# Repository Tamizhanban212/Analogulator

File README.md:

# Analogulator

In an era dominated by digital computation, analog computing remains relevant for specific applications that require real-time processing, low power consumption, and continuous data handling. Unlike digital calculators that rely on discrete logic and binary arithmetic, analog calculators use continuous voltage or current levels to represent data, enabling faster and more efficient computations for certain tasks.

This project, "Analog Calculator," aims to design a calculator using only analog components (e.g., op-amps, MOSFETs, resistors, capacitors) to perform mathematical operations such as addition, subtraction, multiplication, division, and advanced functions like integration and differentiation. By leveraging analog circuits, this project explores a simpler, more efficient approach to computations in specific real-world scenarios.

Hence, we have designed PCB for the analog calculator inside a 11 cm x 11 cm frame and you can see the final product shown below.

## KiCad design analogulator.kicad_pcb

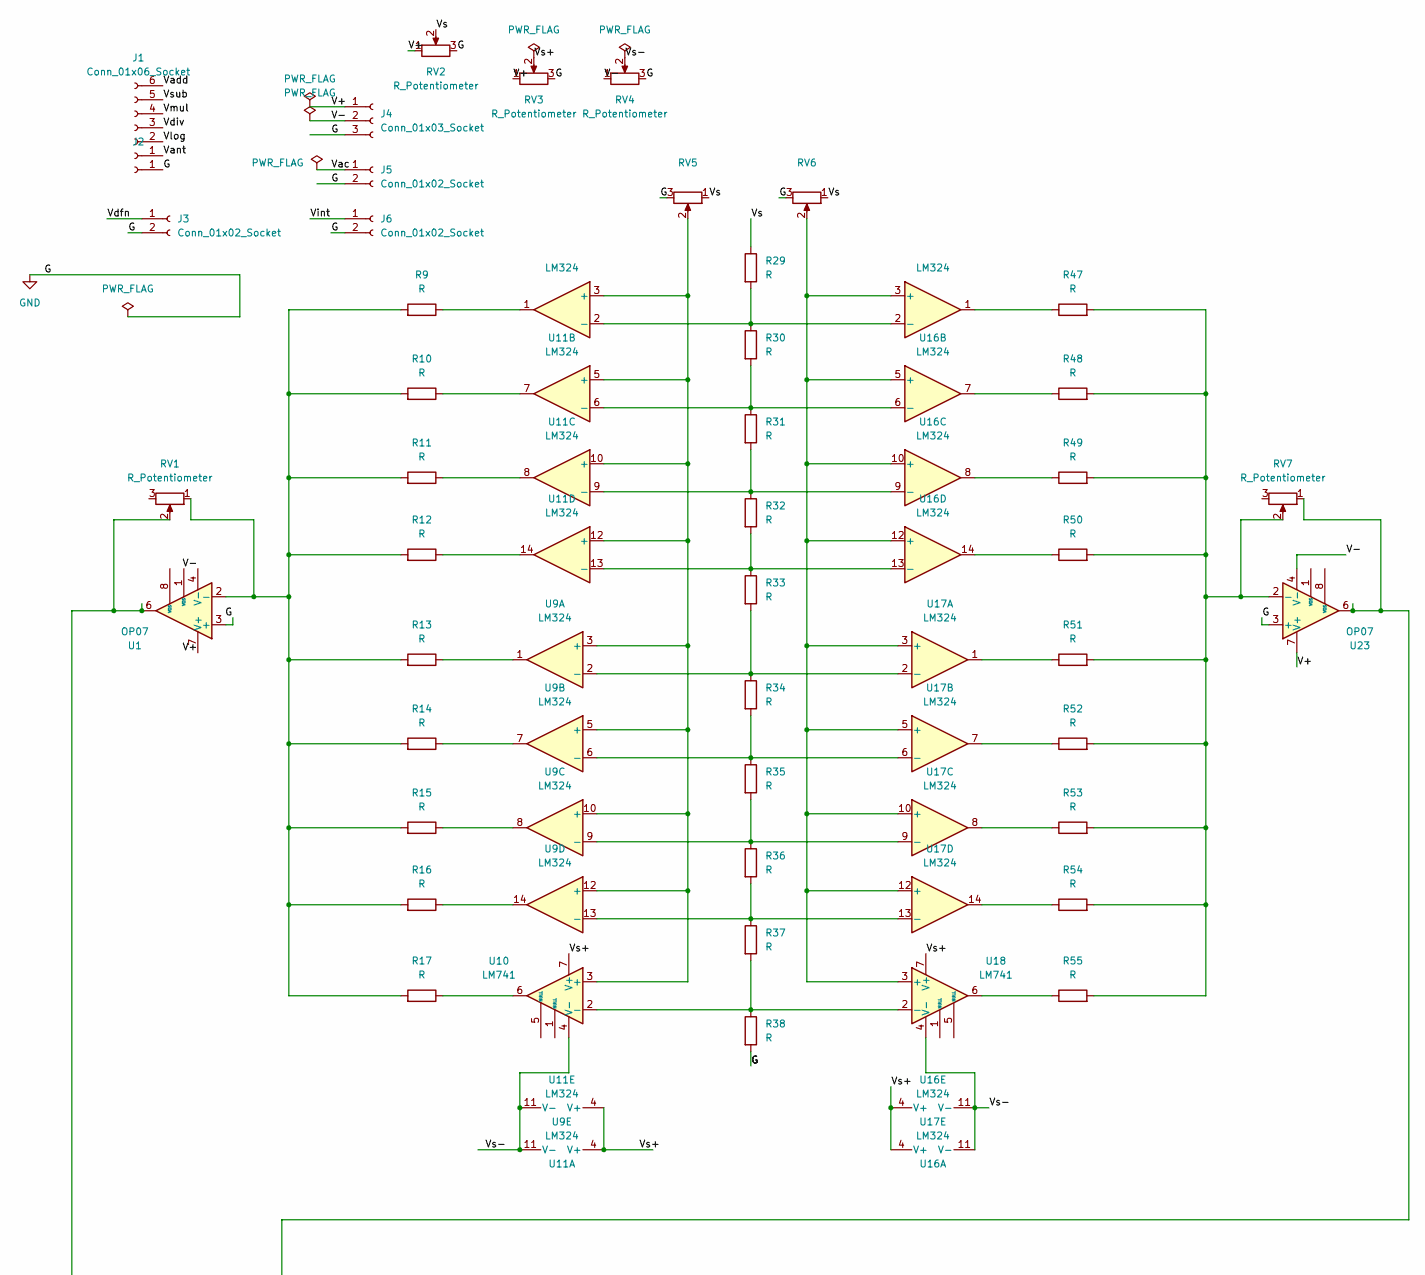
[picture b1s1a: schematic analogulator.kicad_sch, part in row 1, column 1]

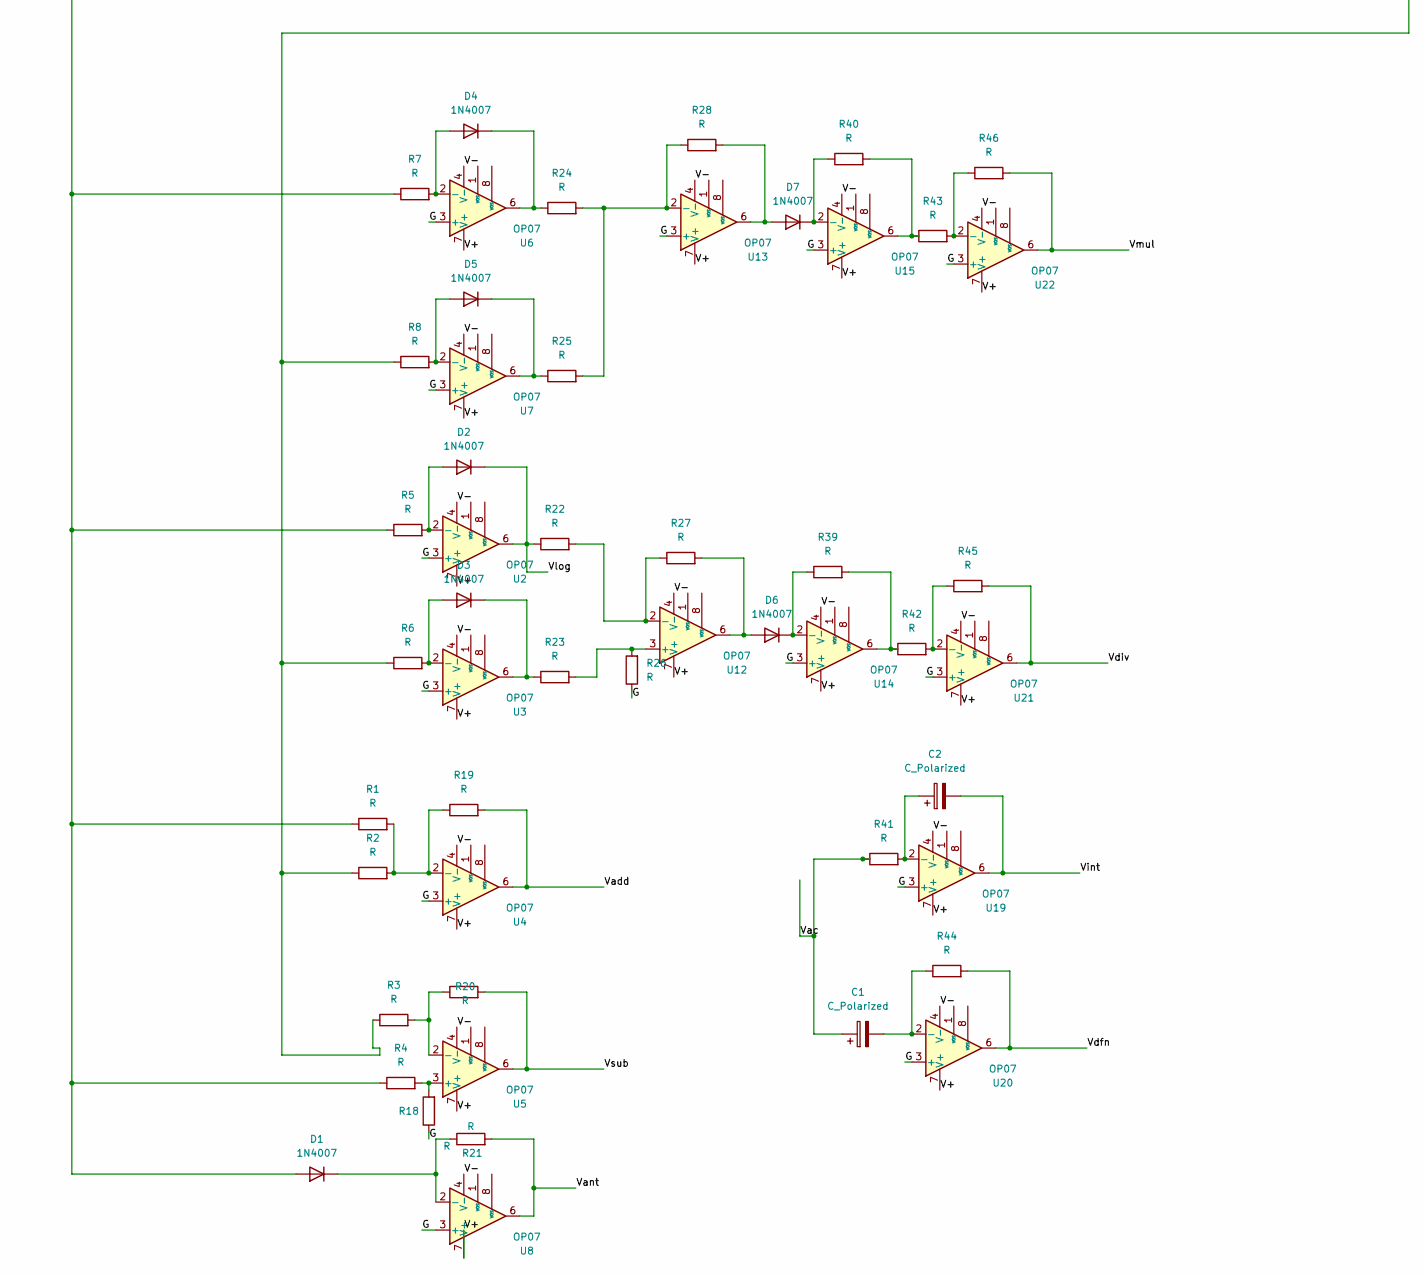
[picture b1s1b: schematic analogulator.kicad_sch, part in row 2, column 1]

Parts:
C1, C2: C_Polarized; CP_Radial_D12.5mm_P7.50mm
D1, D2, D3, D4, D5, D6, D7: 1N4007; D_DO-41_SOD81_P10.16mm_Horizontal
J1: Conn_01x06_Socket; PinSocket_1x06_P2.54mm_Vertical
J2: Conn_01x01_Socket; PinSocket_1x01_P2.54mm_Vertical
J3, J5, J6: Conn_01x02_Socket; PinSocket_1x02_P2.54mm_Vertical
J4: Conn_01x03_Socket; PinSocket_1x03_P2.54mm_Horizontal
R1, R2, R3, R4, R5, R6, R7, R8, R9, R10, R11, R12, R13, R14, R15, R16, R17, R18, R19, R20, R21, R22, R23, R24, R25, R26, R27, R28, R29, R30, R31, R32, R33, R34, R35, R36, R37, R38, R39, R40, R41, R42, R43, R44, R45, R46, R47, R48, R49, R50, R51, R52, R53, R54, R55: R; R_Axial_DIN0309_L9.0mm_D3.2mm_P12.70mm_Horizontal
RV1, RV2, RV3, RV4, RV5, RV6, RV7: R_Potentiometer; Potentiometer_Bourns_3386P_Vertical
U1, U2, U3, U4, U5, U6, U7, U8, U12, U13, U14, U15, U19, U20, U21, U22, U23: OP07; DIP-8_W7.62mm_Socket
U9, U11, U16, U17: LM324; DIP-14_W7.62mm_Socket
U10, U18: LM741; DIP-8_W7.62mm_Socket

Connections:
/V+: J4.1, RV2.1, RV3.1, U1.7 (V+), U2.7 (V+), U3.7 (V+), U4.7 (V+), U5.7 (V+), U6.7 (V+), U7.7 (V+), U8.7 (V+), U12.7 (V+), U13.7 (V+), U14.7 (V+), U15.7 (V+), U19.7 (V+), U20.7 (V+), U21.7 (V+), U22.7 (V+), U23.7 (V+)
/V-: J4.2, RV4.1, U1.4 (V-), U2.4 (V-), U3.4 (V-), U4.4 (V-), U5.4 (V-), U6.4 (V-), U7.4 (V-), U8.4 (V-), U12.4 (V-), U13.4 (V-), U14.4 (V-), U15.4 (V-), U19.4 (V-), U20.4 (V-), U21.4 (V-), U22.4 (V-), U23.4 (V-)
/Vac: C1.1, J5.1, R41.1
/Vadd: J1.6, R19.2, U4.6
/Vant: J1.1, R21.2, U8.6
/Vdfn: J3.1, R44.2, U20.6
/Vdiv: J1.3, R45.2, U21.6
/Vint: C2.2, J6.1, U19.6
/Vlog: D2.1 (K), J1.2, R22.1, U2.6
/Vmul: J1.4, R46.2, U22.6
/Vs: R29.1, RV2.2, RV5.1, RV6.1
/Vs+: RV3.2, U9.4 (V+), U10.7 (V+), U11.4 (V+), U16.4 (V+), U17.4 (V+), U18.7 (V+)
/Vs-: RV4.2, U9.11 (V-), U10.4 (V-), U11.11 (V-), U16.11 (V-), U17.11 (V-), U18.4 (V-)
/Vsub: J1.5, R20.2, U5.6
GND: J2.1, J3.2, J4.3, J5.2, J6.2, R18.1, R26.1, R38.2, RV2.3, RV3.3, RV4.3, RV5.3, RV6.3, U1.3 (+), U2.3 (+), U3.3 (+), U4.3 (+), U6.3 (+), U7.3 (+), U8.3 (+), U13.3 (+), U14.3 (+), U15.3 (+), U19.3 (+), U20.3 (+), U21.3 (+), U22.3 (+), U23.3 (+)
unnamed: D1.2 (A), R1.1, R4.1, R5.1, R7.1, RV1.2, U1.6
unnamed: D1.1 (K), R21.1, U8.2 (-)
unnamed: D2.2 (A), R5.2, U2.2 (-)
unnamed: D3.2 (A), R6.2, U3.2 (-)
unnamed: D3.1 (K), R23.1, U3.6
unnamed: D4.2 (A), R7.2, U6.2 (-)
unnamed: D4.1 (K), R24.1, U6.6
unnamed: D5.2 (A), R8.2, U7.2 (-)
unnamed: D5.1 (K), R25.1, U7.6
unnamed: D6.2 (A), R27.2, U12.6
unnamed: D6.1 (K), R39.1, U14.2 (-)
unnamed: D7.2 (A), R28.2, U13.6
unnamed: D7.1 (K), R40.1, U15.2 (-)
unnamed: R2.1, R3.1, R6.1, R8.1, RV7.1, U23.6
unnamed: R9.1, U11.1
unnamed: R10.1, U11.7
unnamed: R11.1, U11.8
unnamed: R12.1, U11.14
unnamed: R13.1, U9.1
unnamed: R14.1, U9.7
unnamed: R15.1, U9.8
unnamed: R16.1, U9.14
unnamed: R17.1, U10.6
unnamed: R39.2, R42.1, U14.6
unnamed: R40.2, R43.1, U15.6
unnamed: R47.1, U16.1
unnamed: R48.1, U16.7
unnamed: R49.1, U16.8
unnamed: R50.1, U16.14
unnamed: R51.1, U17.1
unnamed: R52.1, U17.7
unnamed: R53.1, U17.8
unnamed: R54.1, U17.14
unnamed: R55.1, U18.6
unnamed: R9.2, R10.2, R11.2, R12.2, R13.2, R14.2, R15.2, R16.2, R17.2, RV1.1, U1.2 (-)
unnamed: R1.2, R2.2, R19.1, U4.2 (-)
unnamed: R4.2, R18.2, U5.3 (+)
unnamed: R3.2, R20.1, U5.2 (-)
unnamed: RV5.2, U9.3 (+), U9.5 (+), U9.10 (+), U9.12 (+), U10.3 (+), U11.3 (+), U11.5 (+), U11.10 (+), U11.12 (+)
unnamed: R37.2, R38.1, U10.2 (-), U18.2 (-)
unnamed: R29.2, R30.1, U11.2 (-), U16.2 (-)
unnamed: R30.2, R31.1, U11.6 (-), U16.6 (-)
unnamed: R31.2, R32.1, U11.9 (-), U16.9 (-)
unnamed: R32.2, R33.1, U11.13 (-), U16.13 (-)
unnamed: R23.2, R26.2, U12.3 (+)
unnamed: R22.2, R27.1, U12.2 (-)
unnamed: R24.2, R25.2, R28.1, U13.2 (-)
unnamed: RV6.2, U16.3 (+), U16.5 (+), U16.10 (+), U16.12 (+), U17.3 (+), U17.5 (+), U17.10 (+), U17.12 (+), U18.3 (+)
unnamed: R33.2, R34.1, U9.2 (-), U17.2 (-)
unnamed: R34.2, R35.1, U9.6 (-), U17.6 (-)
unnamed: R35.2, R36.1, U9.9 (-), U17.9 (-)
unnamed: R36.2, R37.1, U9.13 (-), U17.13 (-)
unnamed: C2.1, R41.2, U19.2 (-)
unnamed: C1.2, R44.1, U20.2 (-)
unnamed: R42.2, R45.1, U21.2 (-)
unnamed: R43.2, R46.1, U22.2 (-)
unnamed: R47.2, R48.2, R49.2, R50.2, R51.2, R52.2, R53.2, R54.2, R55.2, RV7.2, U23.2 (-)

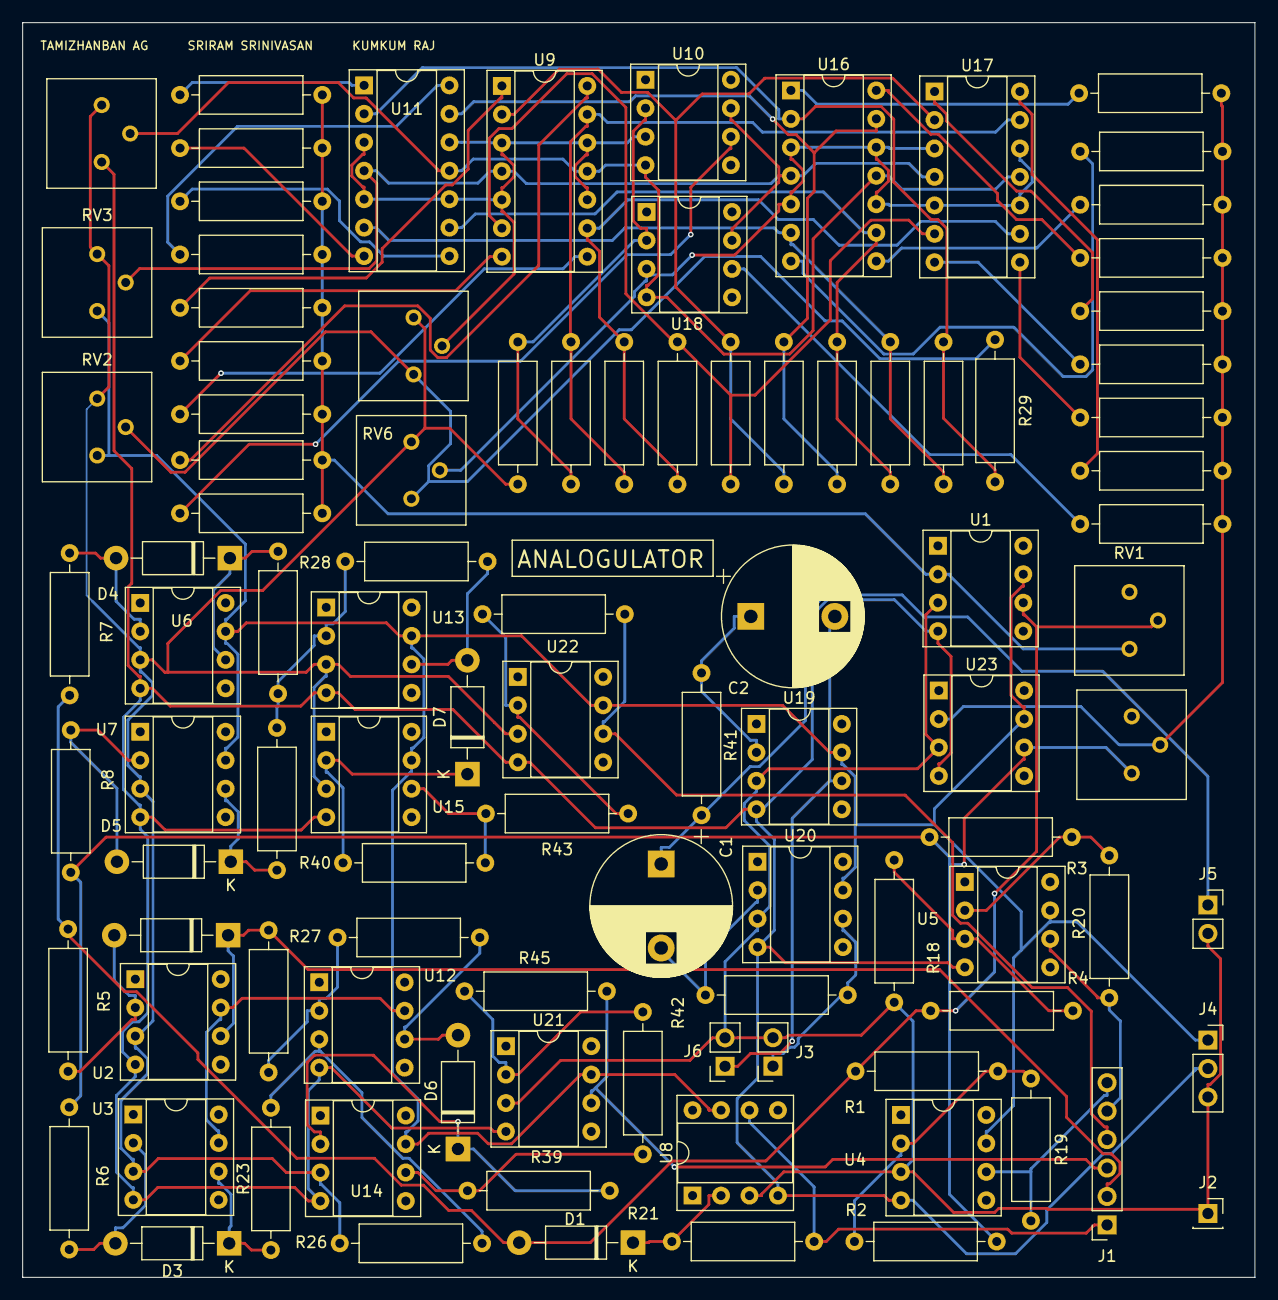
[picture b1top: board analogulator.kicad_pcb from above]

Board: 2 copper layers, 110.0 x 112.0 mm, 100 parts (0 on the bottom side), 72 nets.

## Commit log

2025-01-02 Added all the project files
